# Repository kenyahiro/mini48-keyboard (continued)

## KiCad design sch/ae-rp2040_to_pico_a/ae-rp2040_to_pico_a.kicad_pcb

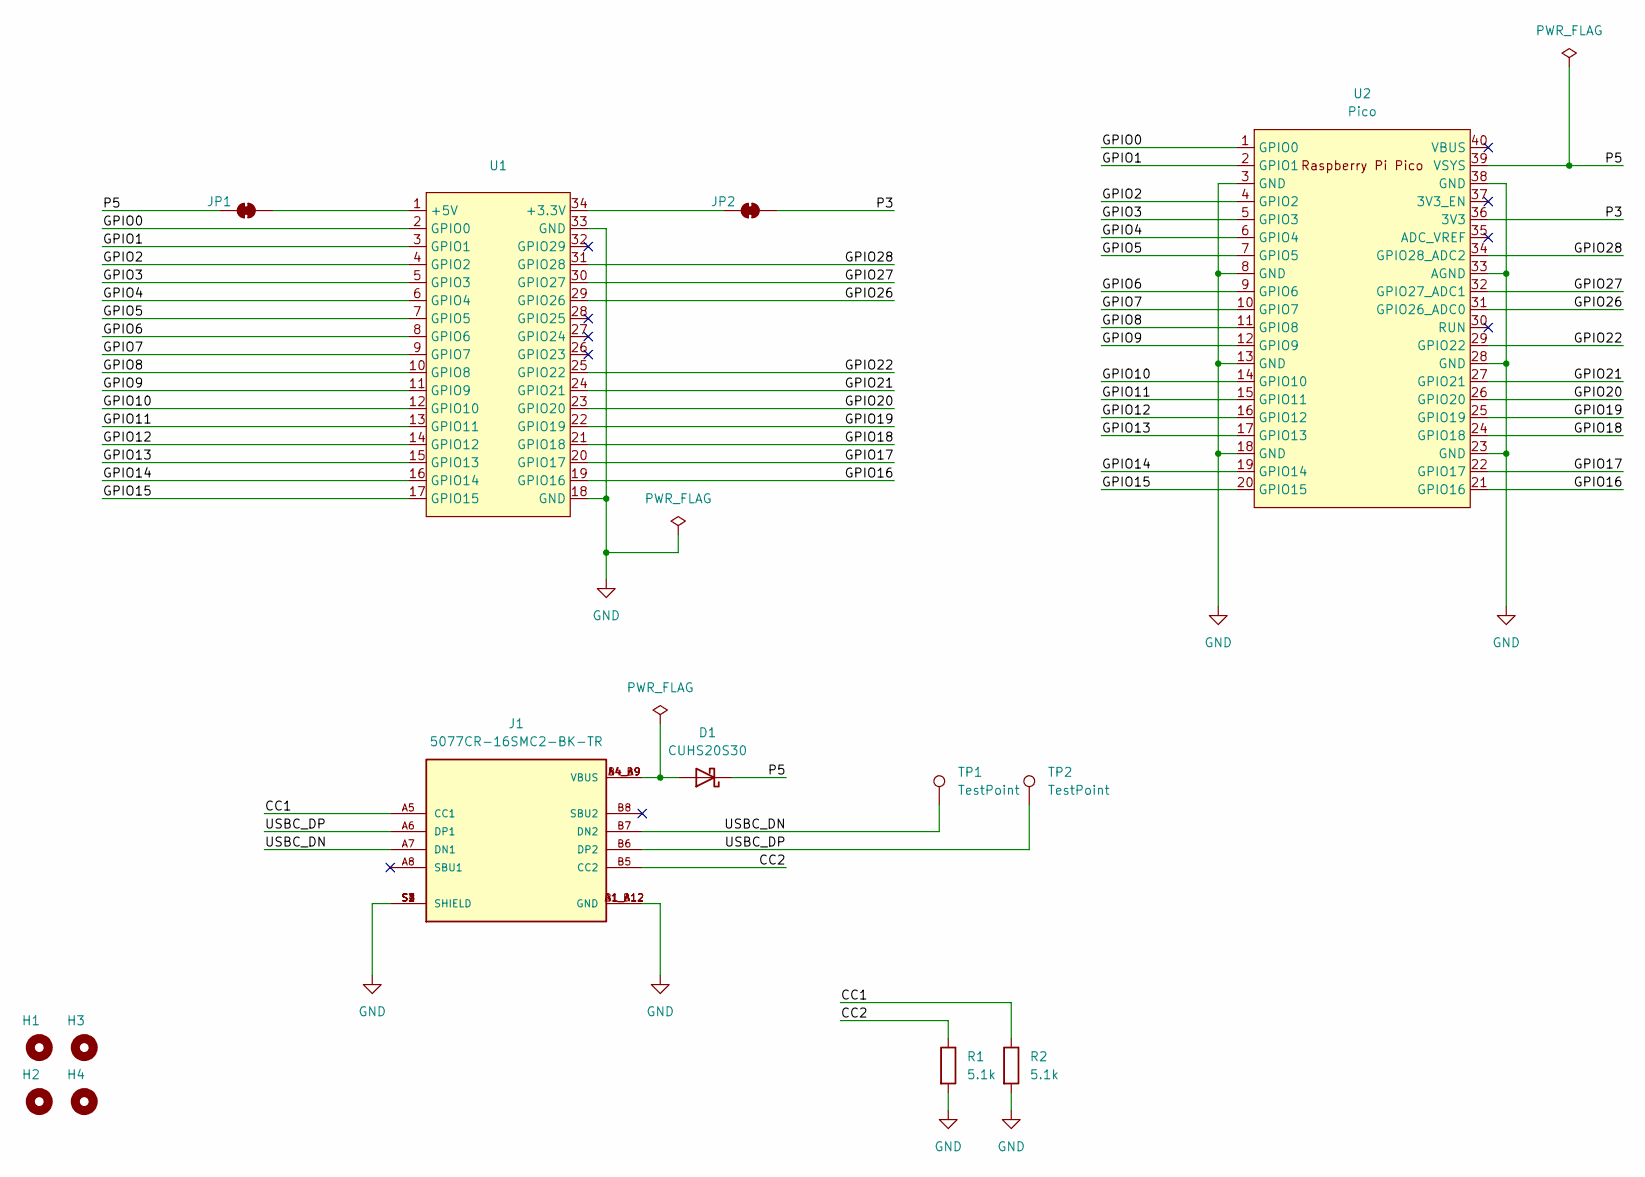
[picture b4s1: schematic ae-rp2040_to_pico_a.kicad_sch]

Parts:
D1: CUHS20S30; D_SOD-323_HandSoldering
H1, H2, H3, H4: MountingHole; MountingHole_3.2mm_M3
J1: 5077CR-16SMC2-BK-TR; NELTRON_5077CR-16SMC2-BK-TR; PARTREV B
JP1, JP2: SolderJumper_2_Bridged; SolderJumper-2_P1.3mm_Bridged_Pad1.0x1.5mm
R1, R2: 5.1k; R_0603_1608Metric
TP1, TP2: TestPoint; TestPoint_Pad_D1.0mm
U1: AE-RP2040
U2: Pico; pico_no_dbg_smd_th_p0.85

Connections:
/CC1: J1.A5 (CC1), R2.1
/CC2: J1.B5 (CC2), R1.1
/GPIO0: U1.2 (GPIO0), U2.1 (GPIO0)
/GPIO1: U1.3 (GPIO1), U2.2 (GPIO1)
/GPIO2: U1.4 (GPIO2), U2.4 (GPIO2)
/GPIO3: U1.5 (GPIO3), U2.5 (GPIO3)
/GPIO4: U1.6 (GPIO4), U2.6 (GPIO4)
/GPIO5: U1.7 (GPIO5), U2.7 (GPIO5)
/GPIO6: U1.8 (GPIO6), U2.9 (GPIO6)
/GPIO7: U1.9 (GPIO7), U2.10 (GPIO7)
/GPIO8: U1.10 (GPIO8), U2.11 (GPIO8)
/GPIO9: U1.11 (GPIO9), U2.12 (GPIO9)
/GPIO10: U1.12 (GPIO10), U2.14 (GPIO10)
/GPIO11: U1.13 (GPIO11), U2.15 (GPIO11)
/GPIO12: U1.14 (GPIO12), U2.16 (GPIO12)
/GPIO13: U1.15 (GPIO13), U2.17 (GPIO13)
/GPIO14: U1.16 (GPIO14), U2.19 (GPIO14)
/GPIO15: U1.17 (GPIO15), U2.20 (GPIO15)
/GPIO16: U1.19 (GPIO16), U2.21 (GPIO16)
/GPIO17: U1.20 (GPIO17), U2.22 (GPIO17)
/GPIO18: U1.21 (GPIO18), U2.24 (GPIO18)
/GPIO19: U1.22 (GPIO19), U2.25 (GPIO19)
/GPIO20: U1.23 (GPIO20), U2.26 (GPIO20)
/GPIO21: U1.24 (GPIO21), U2.27 (GPIO21)
/GPIO22: U1.25 (GPIO22), U2.29 (GPIO22)
/GPIO26: U1.29 (GPIO26), U2.31 (GPIO26_ADC0)
/GPIO27: U1.30 (GPIO27), U2.32 (GPIO27_ADC1)
/GPIO28: U1.31 (GPIO28), U2.34 (GPIO28_ADC2)
/P3: JP2.2 (B), U2.36 (3V3)
/P5: D1.1 (K), JP1.1 (A), U2.39 (VSYS)
/USBC_DN: J1.A7 (DN1), J1.B7 (DN2), TP1.1
/USBC_DP: J1.A6 (DP1), J1.B6 (DP2), TP2.1
GND: J1.A1_B12 (GND), J1.B1_A12 (GND), J1.S1 (SHIELD), J1.S2 (SHIELD), J1.S3 (SHIELD), J1.S4 (SHIELD), R1.2, R2.2, U1.18 (GND), U1.33 (GND), U2.3 (GND), U2.8 (GND), U2.13 (GND), U2.18 (GND), U2.23 (GND), U2.28 (GND), U2.33 (AGND), U2.38 (GND)
unnamed: D1.2 (A), J1.A4_B9 (VBUS), J1.B4_A9 (VBUS)
unnamed: JP1.2 (B), U1.1 (+5V)
unnamed: JP2.1 (A), U1.34 (+3.3V)

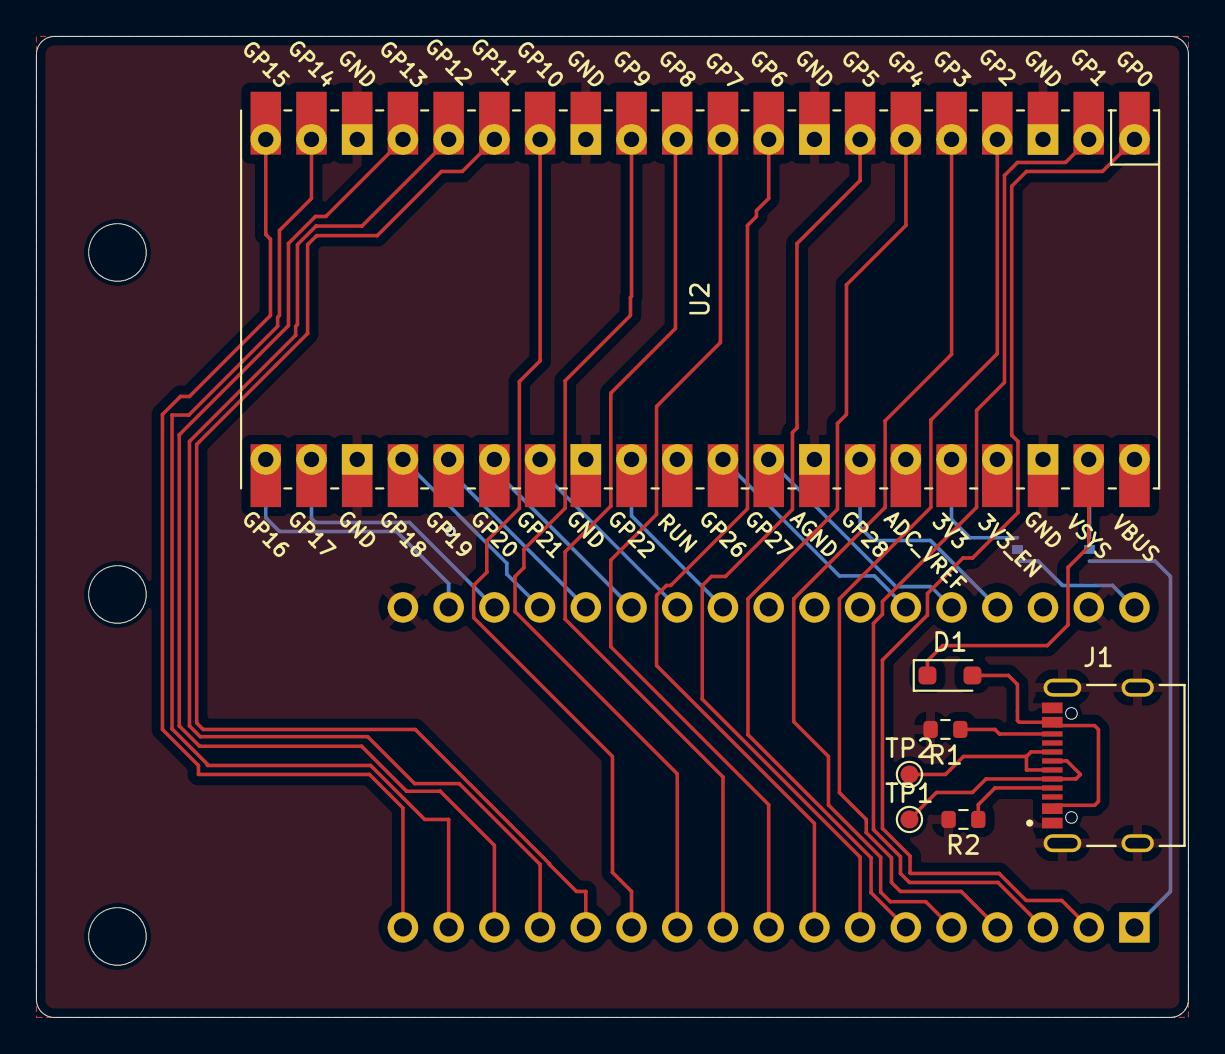
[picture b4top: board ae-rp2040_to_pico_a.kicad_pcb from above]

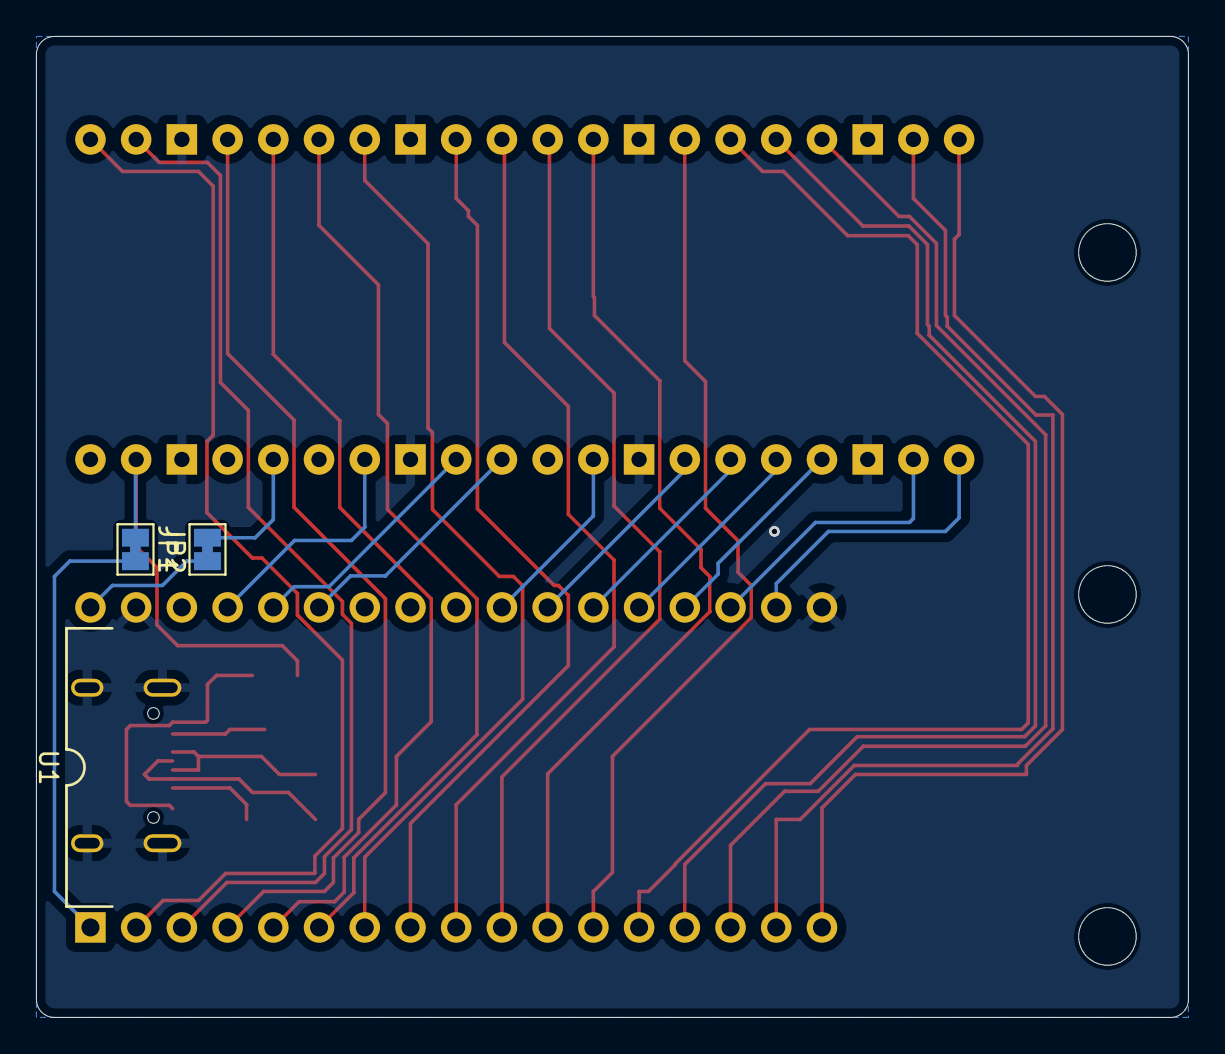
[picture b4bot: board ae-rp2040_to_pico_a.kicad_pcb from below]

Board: 2 copper layers, 64.0 x 54.5 mm, 14 parts (3 on the bottom side), 36 nets.

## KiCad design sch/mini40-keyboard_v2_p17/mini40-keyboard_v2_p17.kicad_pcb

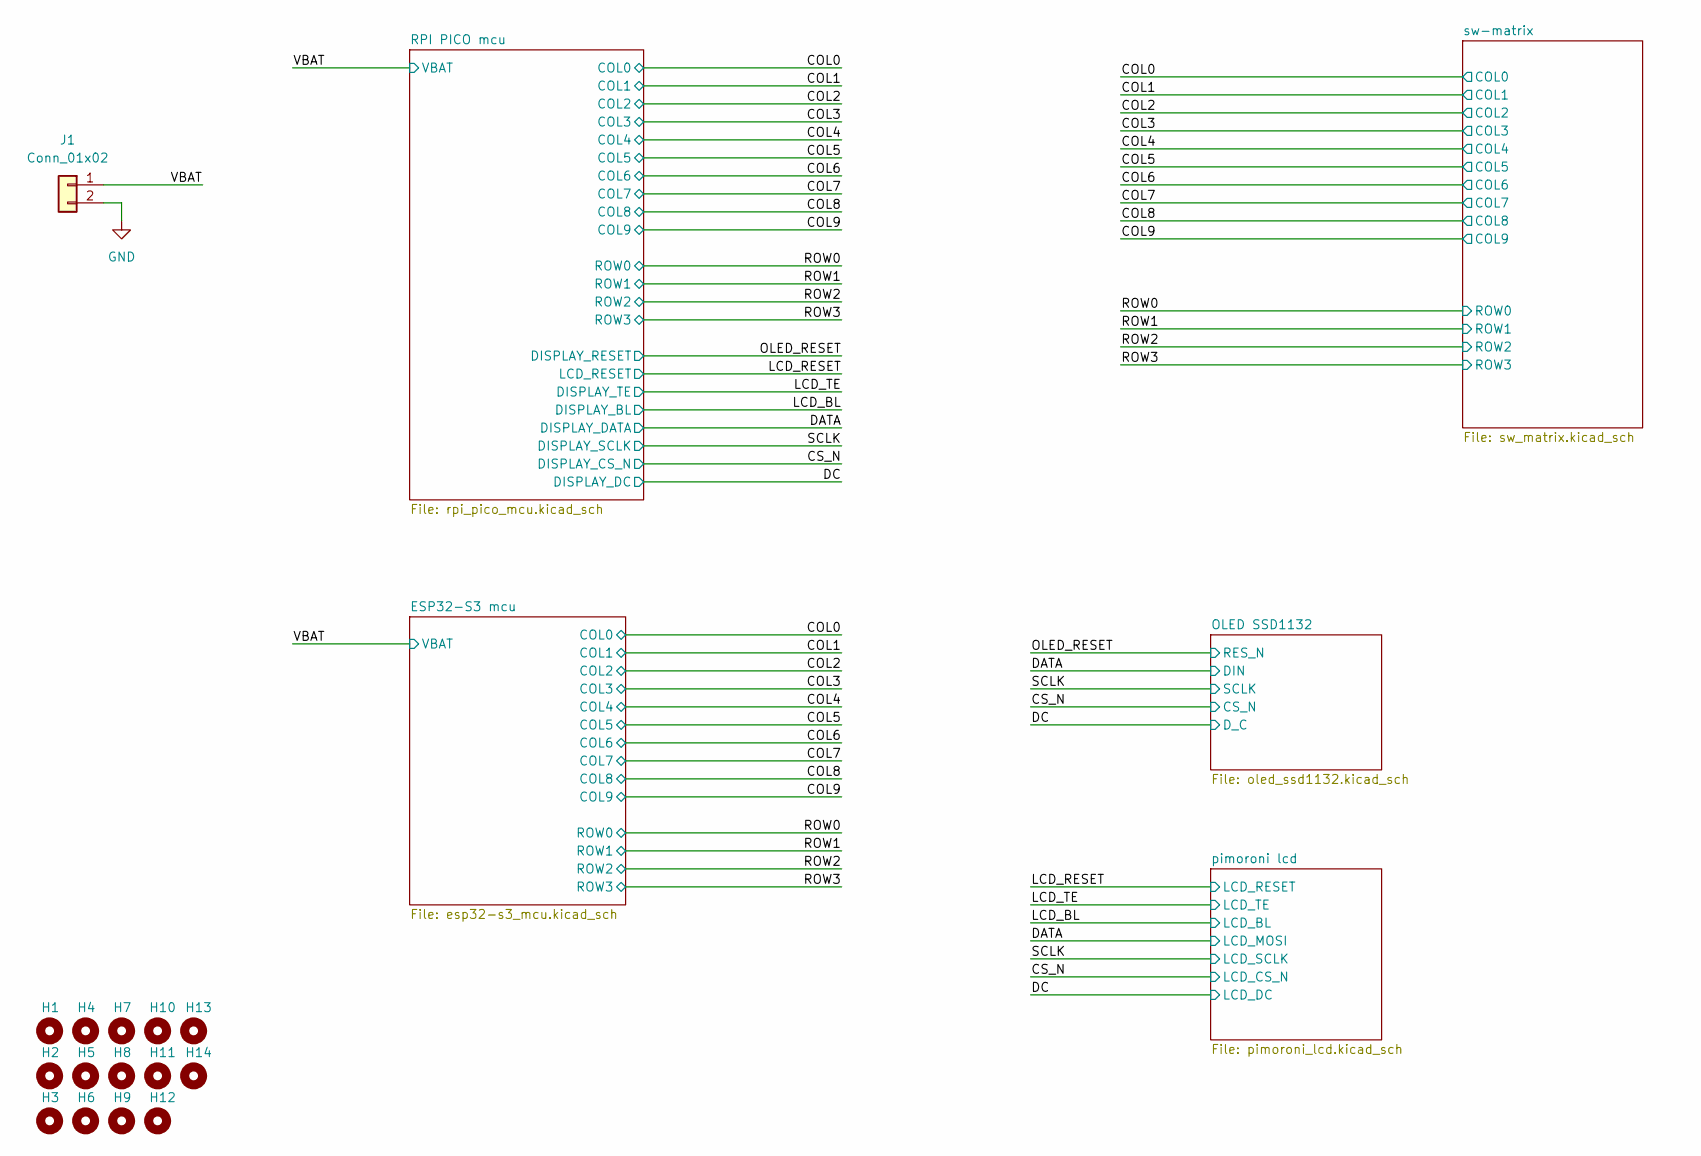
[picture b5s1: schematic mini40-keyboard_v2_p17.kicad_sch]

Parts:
H1, H2, H3, H4, H5, H6, H7, H8, H9, H10, H11, H12, H13, H14: MountingHole; my_MountingHole_2.2mm_M2
J1: Conn_01x02; JST_PH_B2B-PH-K_1x02_P2.00mm_Vertical

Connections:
/VBAT: J1.1; also elsewhere on the board
GND: J1.2; also elsewhere on the board

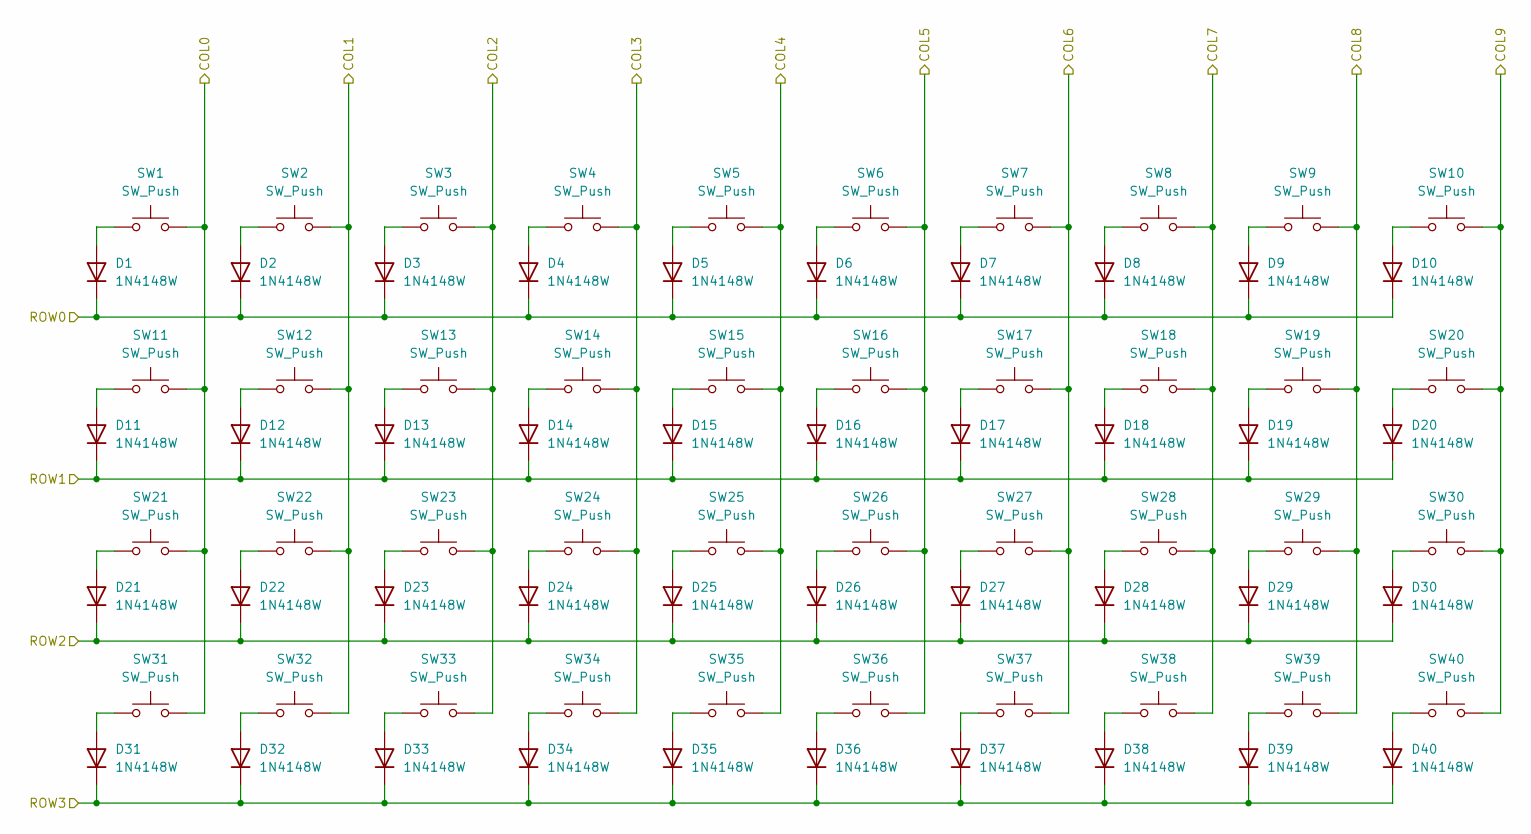
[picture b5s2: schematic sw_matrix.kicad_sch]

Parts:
D1, D2, D3, D4, D5, D6, D7, D8, D9, D10, D11, D12, D13, D14, D15, D16, D17, D18, D19, D20, D21, D22, D23, D24, D25, D26, D27, D28, D29, D30, D31, D32, D33, D34, D35, D36, D37, D38, D39, D40: 1N4148W; D_SOD-123
SW1, SW2, SW3, SW4, SW5, SW6, SW7, SW8, SW9, SW10, SW11, SW12, SW13, SW14, SW15, SW16, SW17, SW18, SW19, SW20, SW21, SW22, SW23, SW24, SW25, SW26, SW27, SW28, SW29, SW30, SW31, SW32, SW33, SW34, SW35, SW36, SW37, SW38, SW39, SW40: SW_Push; SW_Hotswap_Kailh_Choc_V1V2

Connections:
/COL0: SW1.2, SW11.2, SW21.2, SW31.2; also elsewhere on the board
/COL1: SW2.2, SW12.2, SW22.2, SW32.2; also elsewhere on the board
/COL2: SW3.2, SW13.2, SW23.2, SW33.2; also elsewhere on the board
/COL3: SW4.2, SW14.2, SW24.2, SW34.2; also elsewhere on the board
/COL4: SW5.2, SW15.2, SW25.2, SW35.2; also elsewhere on the board
/COL5: SW6.2, SW16.2, SW26.2, SW36.2; also elsewhere on the board
/COL6: SW7.2, SW17.2, SW27.2, SW37.2; also elsewhere on the board
/COL7: SW8.2, SW18.2, SW28.2, SW38.2; also elsewhere on the board
/COL8: SW9.2, SW19.2, SW29.2, SW39.2; also elsewhere on the board
/COL9: SW10.2, SW20.2, SW30.2, SW40.2; also elsewhere on the board
/ROW0: D1.1 (K), D2.1 (K), D3.1 (K), D4.1 (K), D5.1 (K), D6.1 (K), D7.1 (K), D8.1 (K), D9.1 (K), D10.1 (K); also elsewhere on the board
/ROW1: D11.1 (K), D12.1 (K), D13.1 (K), D14.1 (K), D15.1 (K), D16.1 (K), D17.1 (K), D18.1 (K), D19.1 (K), D20.1 (K); also elsewhere on the board
/ROW2: D21.1 (K), D22.1 (K), D23.1 (K), D24.1 (K), D25.1 (K), D26.1 (K), D27.1 (K), D28.1 (K), D29.1 (K), D30.1 (K); also elsewhere on the board
/ROW3: D31.1 (K), D32.1 (K), D33.1 (K), D34.1 (K), D35.1 (K), D36.1 (K), D37.1 (K), D38.1 (K), D39.1 (K), D40.1 (K); also elsewhere on the board
unnamed: D1.2 (A), SW1.1
unnamed: D2.2 (A), SW2.1
unnamed: D3.2 (A), SW3.1
unnamed: D4.2 (A), SW4.1
unnamed: D5.2 (A), SW5.1
unnamed: D6.2 (A), SW6.1
unnamed: D7.2 (A), SW7.1
unnamed: D8.2 (A), SW8.1
unnamed: D9.2 (A), SW9.1
unnamed: D10.2 (A), SW10.1
unnamed: D11.2 (A), SW11.1
unnamed: D12.2 (A), SW12.1
unnamed: D13.2 (A), SW13.1
unnamed: D14.2 (A), SW14.1
unnamed: D15.2 (A), SW15.1
unnamed: D16.2 (A), SW16.1
unnamed: D17.2 (A), SW17.1
unnamed: D18.2 (A), SW18.1
unnamed: D19.2 (A), SW19.1
unnamed: D20.2 (A), SW20.1
unnamed: D21.2 (A), SW21.1
unnamed: D22.2 (A), SW22.1
unnamed: D23.2 (A), SW23.1
unnamed: D24.2 (A), SW24.1
unnamed: D25.2 (A), SW25.1
unnamed: D26.2 (A), SW26.1
unnamed: D27.2 (A), SW27.1
unnamed: D28.2 (A), SW28.1
unnamed: D29.2 (A), SW29.1
unnamed: D30.2 (A), SW30.1
unnamed: D31.2 (A), SW31.1
unnamed: D32.2 (A), SW32.1
unnamed: D33.2 (A), SW33.1
unnamed: D34.2 (A), SW34.1
unnamed: D35.2 (A), SW35.1
unnamed: D36.2 (A), SW36.1
unnamed: D37.2 (A), SW37.1
unnamed: D38.2 (A), SW38.1
unnamed: D39.2 (A), SW39.1
unnamed: D40.2 (A), SW40.1

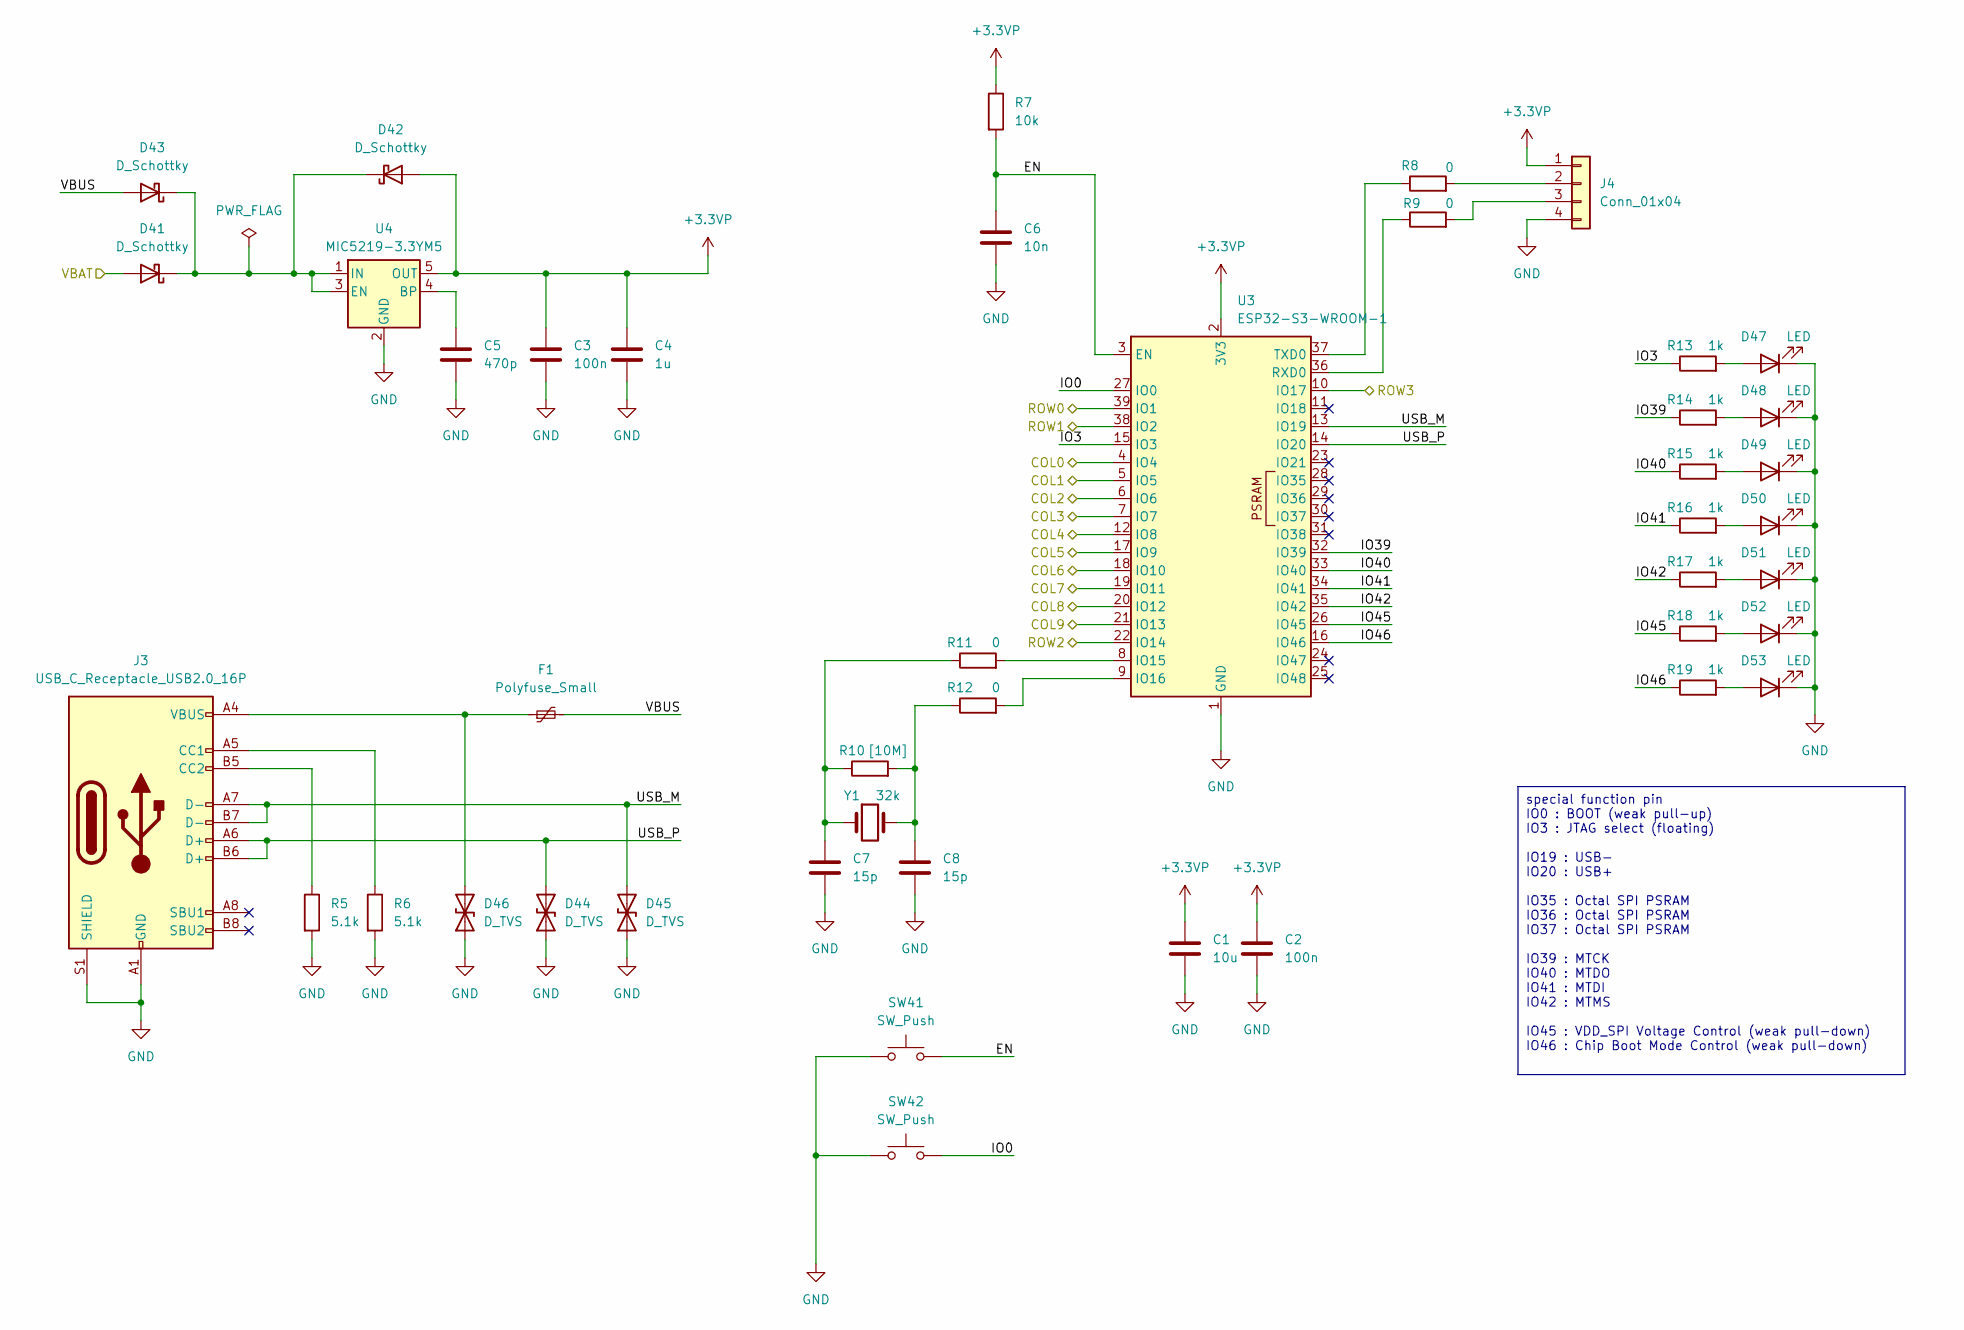
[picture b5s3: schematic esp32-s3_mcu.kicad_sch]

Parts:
C1: 10u; C_0603_1608Metric_Pad1.08x0.95mm_HandSolder
C2, C3: 100n; C_0603_1608Metric_Pad1.08x0.95mm_HandSolder
C4: 1u; C_0603_1608Metric_Pad1.08x0.95mm_HandSolder
C5: 470p; C_0603_1608Metric_Pad1.08x0.95mm_HandSolder
C6: 10n; C_0603_1608Metric_Pad1.08x0.95mm_HandSolder
C7, C8: 15p; C_0603_1608Metric_Pad1.08x0.95mm_HandSolder
D41, D42, D43: D_Schottky; D_SOD-123
D44, D45, D46: D_TVS; D_SOD-123
D47, D48, D49, D50, D51, D52, D53: LED; LED_0603_1608Metric_Pad1.05x0.95mm_HandSolder
F1: Polyfuse_Small; Fuse_Littelfuse-NANO2-451_453
J3: USB_C_Receptacle_USB2.0_16P; USB_C_Receptacle_XKB_U262-16XN-4BVC11
J4: Conn_01x04; JST_XH_B4B-XH-A_1x04_P2.50mm_Vertical
R5, R6: 5.1k; R_0603_1608Metric
R7: 10k; R_0603_1608Metric
R8, R9, R11, R12: 0; R_0603_1608Metric
R10: [10M]; R_0603_1608Metric
R13, R14, R15, R16, R17, R18, R19: 1k; R_0603_1608Metric
SW41, SW42: SW_Push; SW_Push_SPST_NO_Alps_SKRK
U3: ESP32-S3-WROOM-1
U4: MIC5219-3.3YM5; SOT-23-5
Y1: 32k; Crystal_SMD_2012-2Pin_2.0x1.2mm_HandSoldering

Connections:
+3.3VP: C1.1, C2.1, C3.1, C4.1, D42.2 (A), J4.1, R7.1, U3.2 (3V3), U4.5 (OUT)
/COL0: U3.4 (IO4); also elsewhere on the board
/COL1: U3.5 (IO5); also elsewhere on the board
/COL2: U3.6 (IO6); also elsewhere on the board
/COL3: U3.7 (IO7); also elsewhere on the board
/COL4: U3.12 (IO8); also elsewhere on the board
/COL5: U3.17 (IO9); also elsewhere on the board
/COL6: U3.18 (IO10); also elsewhere on the board
/COL7: U3.19 (IO11); also elsewhere on the board
/COL8: U3.20 (IO12); also elsewhere on the board
/COL9: U3.21 (IO13); also elsewhere on the board
/ESP32-S3 mcu/EN: C6.1, R7.2, SW41.2, U3.3 (EN)
/ESP32-S3 mcu/IO0: SW42.2, U3.27 (IO0)
/ESP32-S3 mcu/IO3: R13.1, U3.15 (IO3)
/ESP32-S3 mcu/IO39: R14.1, U3.32 (IO39)
/ESP32-S3 mcu/IO40: R15.1, U3.33 (IO40)
/ESP32-S3 mcu/IO41: R16.1, U3.34 (IO41)
/ESP32-S3 mcu/IO42: R17.1, U3.35 (IO42)
/ESP32-S3 mcu/IO45: R18.1, U3.26 (IO45)
/ESP32-S3 mcu/IO46: R19.1, U3.16 (IO46)
/ESP32-S3 mcu/USB_M: D45.2 (A2), J3.A7 (D-), J3.B7 (D-), U3.13 (IO19)
/ESP32-S3 mcu/USB_P: D44.2 (A2), J3.A6 (D+), J3.B6 (D+), U3.14 (IO20)
/ESP32-S3 mcu/VBUS: D43.2 (A), F1.2
/ROW0: U3.39 (IO1); also elsewhere on the board
/ROW1: U3.38 (IO2); also elsewhere on the board
/ROW2: U3.22 (IO14); also elsewhere on the board
/ROW3: U3.10 (IO17); also elsewhere on the board
/VBAT: D41.2 (A); also elsewhere on the board
GND: C1.2, C2.2, C3.2, C4.2, C5.2, C6.2, C7.2, C8.2, D44.1 (A1), D45.1 (A1), D46.1 (A1), D47.1 (K), D48.1 (K), D49.1 (K), D50.1 (K), D51.1 (K), D52.1 (K), D53.1 (K), J3.A1 (GND), J3.A12 (GND), J3.B1 (GND), J3.B12 (GND), J3.S1 (SHIELD), J4.4, R5.2, R6.2, SW41.1, SW42.1, U3.1 (GND), U3.40 (GND), U3.41 (GND), U4.2 (GND); also elsewhere on the board
unnamed: C7.1, R10.1, R11.1, Y1.1
unnamed: C8.1, R10.2, R12.1, Y1.2
unnamed: D41.1 (K), D42.1 (K), D43.1 (K), U4.1 (IN), U4.3 (EN)
unnamed: D46.2 (A2), F1.1, J3.A4 (VBUS), J3.A9 (VBUS), J3.B4 (VBUS), J3.B9 (VBUS)
unnamed: D47.2 (A), R13.2
unnamed: D48.2 (A), R14.2
unnamed: D49.2 (A), R15.2
unnamed: D50.2 (A), R16.2
unnamed: D51.2 (A), R17.2
unnamed: D52.2 (A), R18.2
unnamed: D53.2 (A), R19.2
unnamed: J3.A5 (CC1), R6.1
unnamed: J3.B5 (CC2), R5.1
unnamed: J4.2, R8.2
unnamed: J4.3, R9.2
unnamed: R11.2, U3.8 (IO15)
unnamed: R12.2, U3.9 (IO16)
unnamed: R9.1, U3.36 (RXD0)
unnamed: R8.1, U3.37 (TXD0)
unnamed: C5.1, U4.4 (BP)

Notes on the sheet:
special function pin IO0 : BOOT (weak pull-up) IO3 : JTAG select (floating) IO19 : USB- IO20 : USB+ IO35 : Octal SPI PSRAM IO36 : Octal SPI PSRAM IO37 : Octal SPI PSRAM IO39 : MTCK IO40 : MTDO IO41 : MTDI IO42 : MTMS IO45 : VDD_SPI Voltage Control (weak pull-down) IO46 : Chip Boot Mode Control (wea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

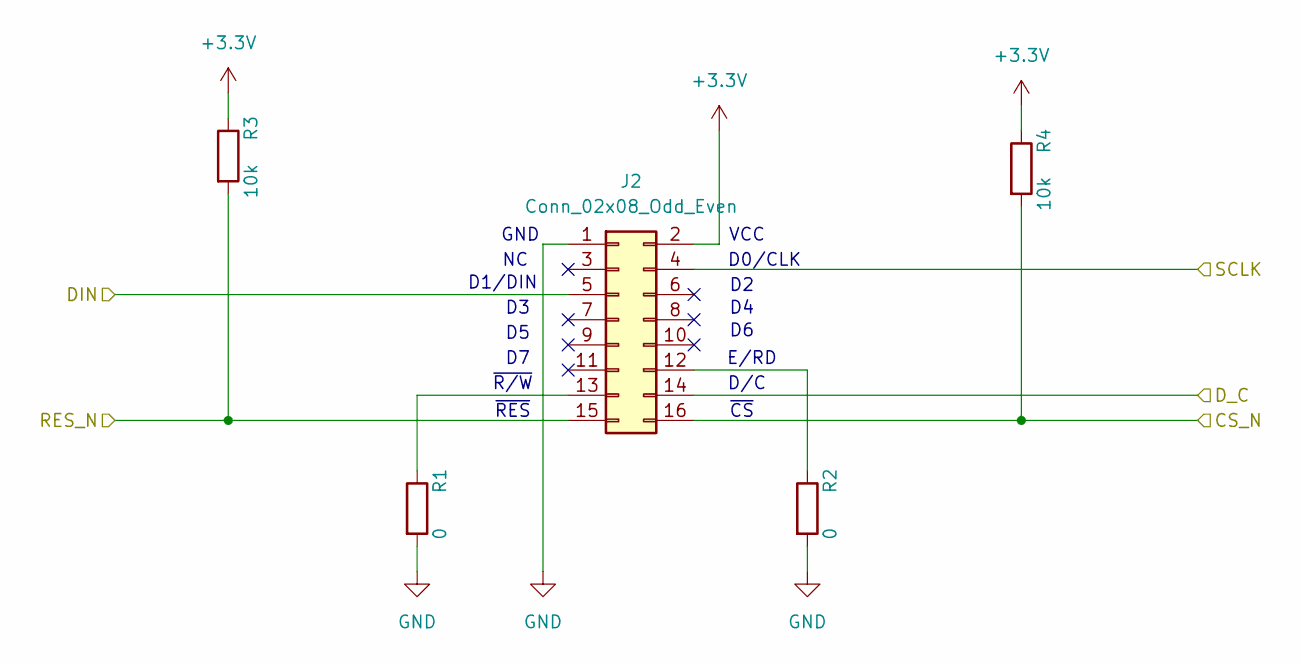
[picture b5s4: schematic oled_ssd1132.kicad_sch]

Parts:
J2: Conn_02x08_Odd_Even; oled_PinSocket_2x08_P2.54mm_Vertical
R1, R2: 0; R_0603_1608Metric
R3, R4: 10k; R_0603_1608Metric

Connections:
+3.3V: J2.2, R3.1, R4.1; also elsewhere on the board
/CS_N: J2.16, R4.2; also elsewhere on the board
/DATA: J2.5; also elsewhere on the board
/DC: J2.14; also elsewhere on the board
/OLED_RESET: J2.15, R3.2; also elsewhere on the board
/SCLK: J2.4; also elsewhere on the board
GND: J2.1, R1.2, R2.2; also elsewhere on the board
unnamed: J2.12, R2.1
unnamed: J2.13, R1.1

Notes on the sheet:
GND
D1/DIN
D0/CLK
~{RES}
~{CS}
VCC
D/C
E/RD
~{R/W}

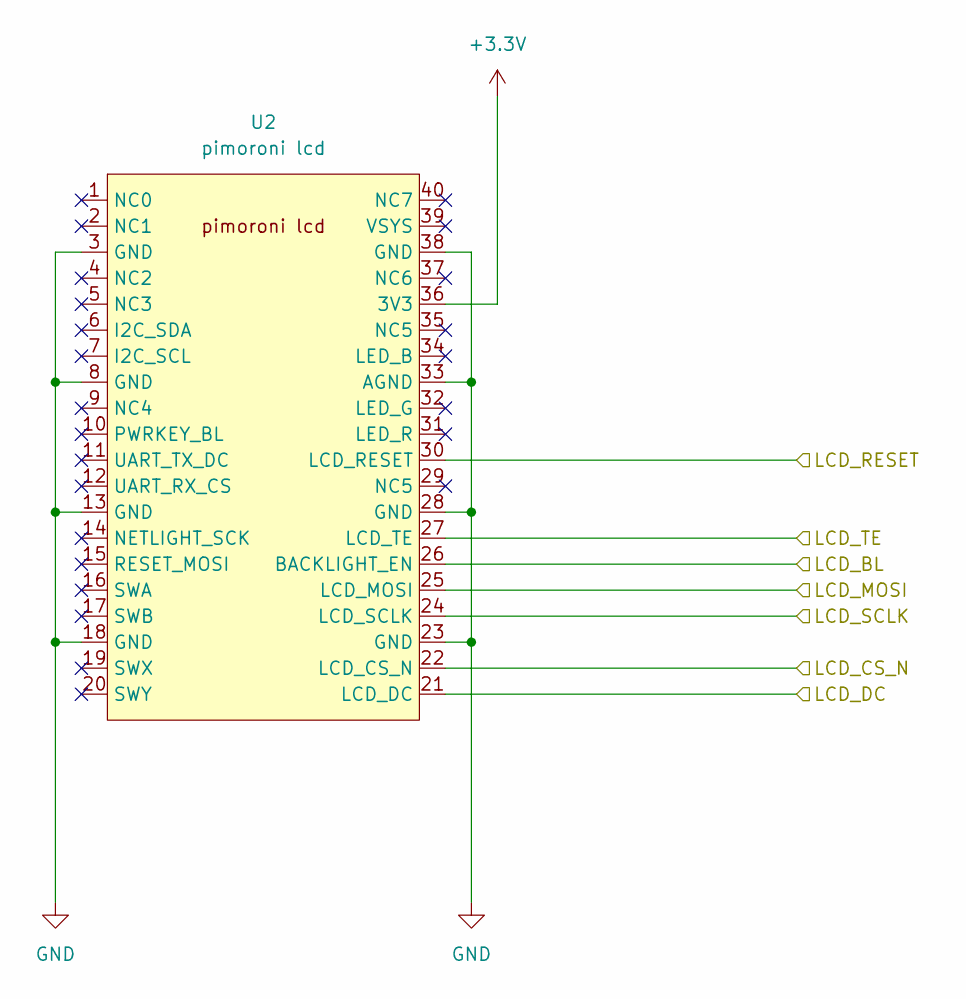
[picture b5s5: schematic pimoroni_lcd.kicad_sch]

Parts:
U2: pimoroni lcd; pimoroni_lcd_p0.85

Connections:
+3.3V: U2.36 (3V3); also elsewhere on the board
/CS_N: U2.22 (LCD_CS_N); also elsewhere on the board
/DATA: U2.25 (LCD_MOSI); also elsewhere on the board
/DC: U2.21 (LCD_DC); also elsewhere on the board
/LCD_BL: U2.26 (BACKLIGHT_EN); also elsewhere on the board
/LCD_RESET: U2.30 (LCD_RESET); also elsewhere on the board
/LCD_TE: U2.27 (LCD_TE); also elsewhere on the board
/SCLK: U2.24 (LCD_SCLK); also elsewhere on the board
GND: U2.3 (GND), U2.8 (GND), U2.13 (GND), U2.18 (GND), U2.23 (GND), U2.28 (GND), U2.33 (AGND), U2.38 (GND); also elsewhere on the board

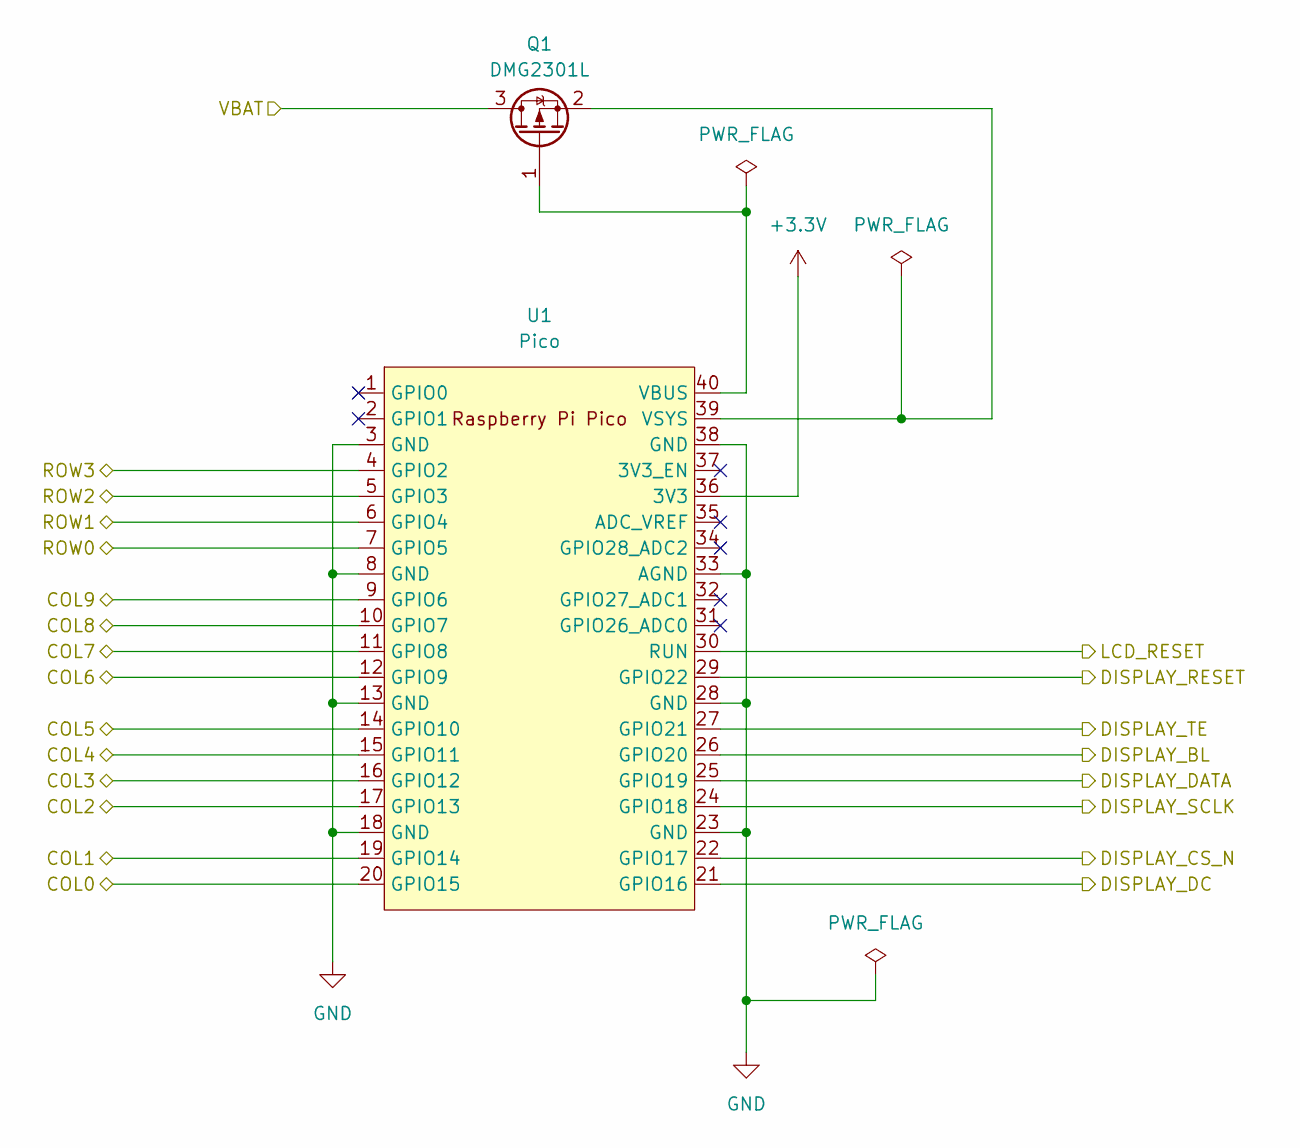
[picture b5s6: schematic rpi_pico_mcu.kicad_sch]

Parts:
Q1: DMG2301L; SOT-23
U1: Pico; pico_no_dbg_smd_th_p0.85

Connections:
+3.3V: U1.36 (3V3); also elsewhere on the board
/COL0: U1.20 (GPIO15); also elsewhere on the board
/COL1: U1.19 (GPIO14); also elsewhere on the board
/COL2: U1.17 (GPIO13); also elsewhere on the board
/COL3: U1.16 (GPIO12); also elsewhere on the board
/COL4: U1.15 (GPIO11); also elsewhere on the board
/COL5: U1.14 (GPIO10); also elsewhere on the board
/COL6: U1.12 (GPIO9); also elsewhere on the board
/COL7: U1.11 (GPIO8); also elsewhere on the board
/COL8: U1.10 (GPIO7); also elsewhere on the board
/COL9: U1.9 (GPIO6); also elsewhere on the board
/CS_N: U1.22 (GPIO17); also elsewhere on the board
/DATA: U1.25 (GPIO19); also elsewhere on the board
/DC: U1.21 (GPIO16); also elsewhere on the board
/LCD_BL: U1.26 (GPIO20); also elsewhere on the board
/LCD_RESET: U1.30 (RUN); also elsewhere on the board
/LCD_TE: U1.27 (GPIO21); also elsewhere on the board
/OLED_RESET: U1.29 (GPIO22); also elsewhere on the board
/ROW0: U1.7 (GPIO5); also elsewhere on the board
/ROW1: U1.6 (GPIO4); also elsewhere on the board
/ROW2: U1.5 (GPIO3); also elsewhere on the board
/ROW3: U1.4 (GPIO2); also elsewhere on the board
/SCLK: U1.24 (GPIO18); also elsewhere on the board
/VBAT: Q1.3 (D); also elsewhere on the board
GND: U1.3 (GND), U1.8 (GND), U1.13 (GND), U1.18 (GND), U1.23 (GND), U1.28 (GND), U1.33 (AGND), U1.38 (GND); also elsewhere on the board
unnamed: Q1.1 (G), U1.40 (VBUS)
unnamed: Q1.2 (S), U1.39 (VSYS)

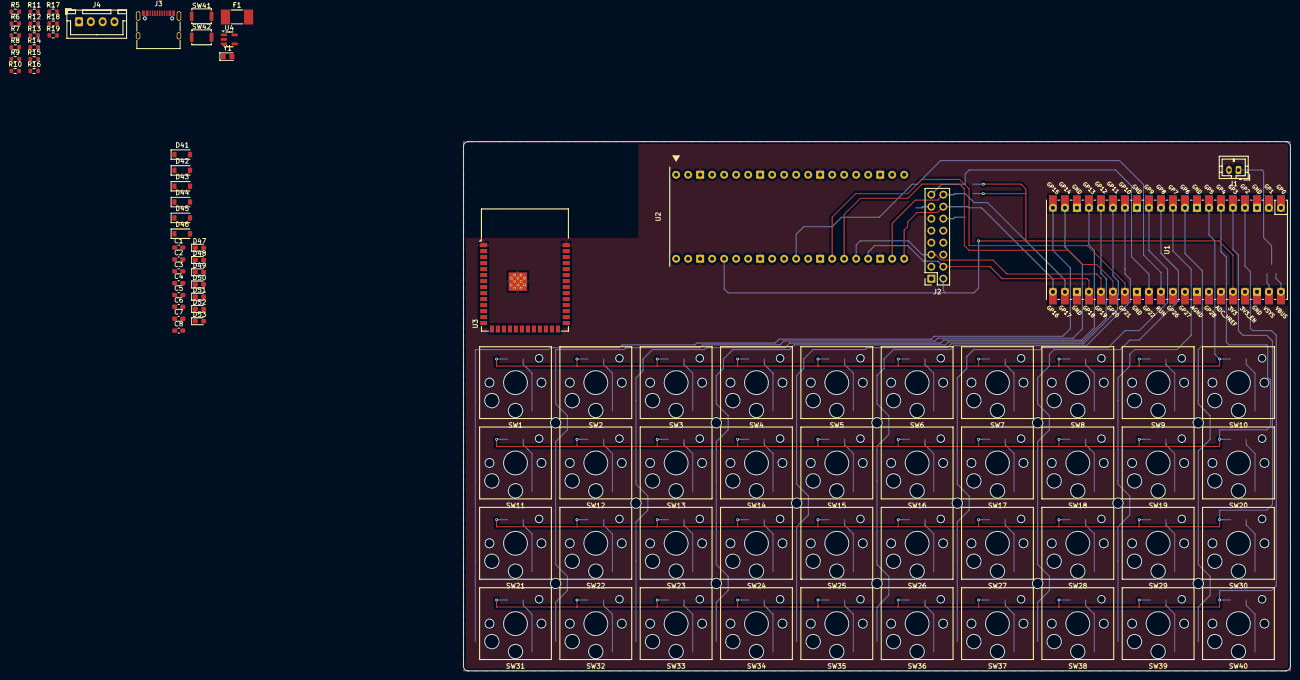
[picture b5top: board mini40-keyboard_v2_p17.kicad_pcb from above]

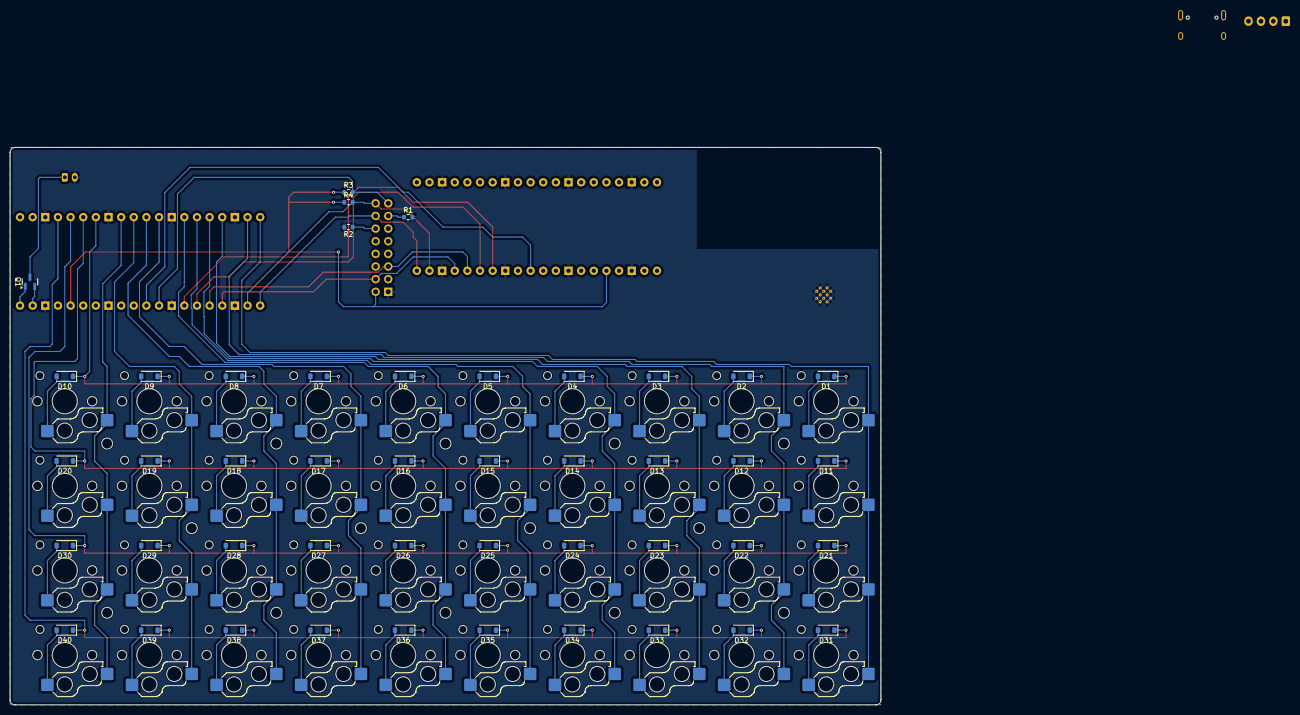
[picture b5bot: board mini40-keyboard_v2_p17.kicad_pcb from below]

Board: 2 copper layers, 175.0 x 112.0 mm, 147 parts (45 on the bottom side), 102 nets.
